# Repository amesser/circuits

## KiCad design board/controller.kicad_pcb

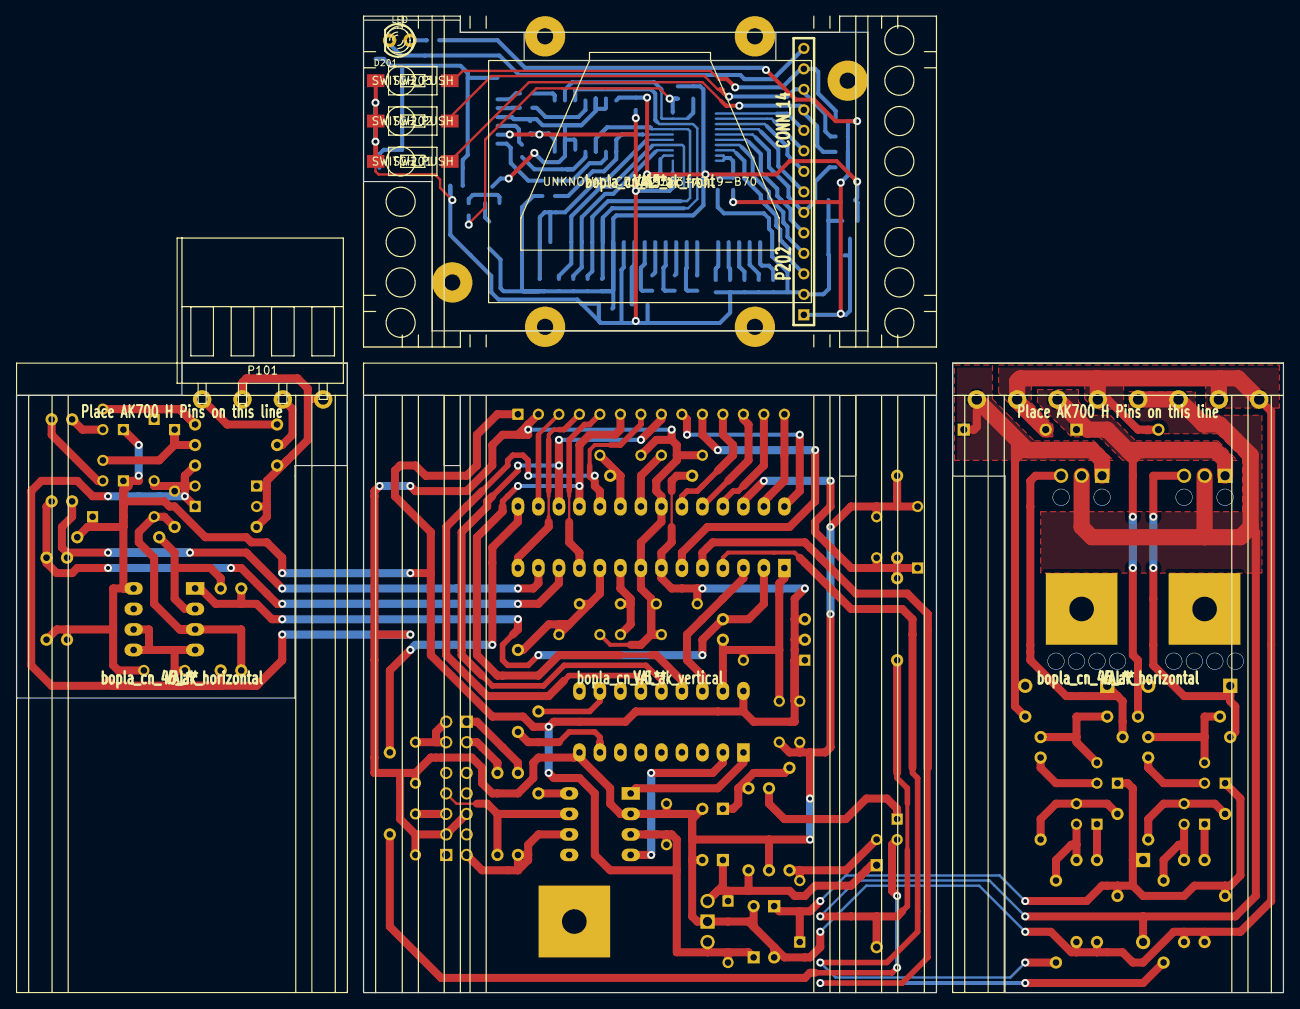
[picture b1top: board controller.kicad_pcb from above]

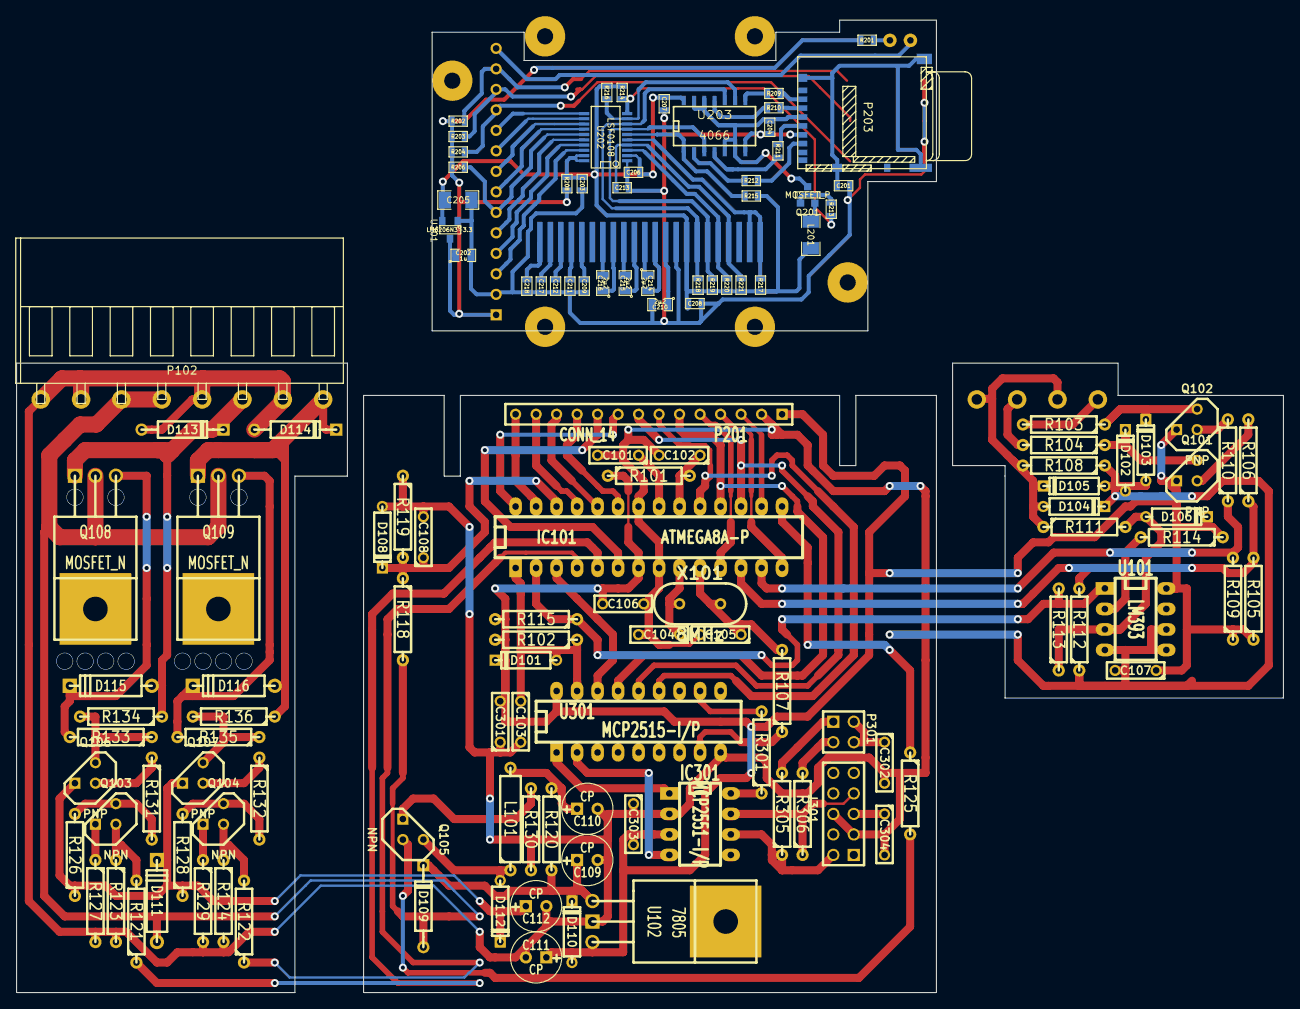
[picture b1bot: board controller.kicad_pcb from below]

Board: 2 copper layers, 157.0 x 120.5 mm, 142 parts (131 on the bottom side), 116 nets.

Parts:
C101, C102, C103, C106, C107, C108, C301, C302, C303, C304: 100n; C2
C104, C105: C; C2
C109, C110, C111, C112: CP; C1V7
C201, C203, C204, C206, C207, C208, C213: 100n; SM0603
C202: 1u; SM0805
C205: 10u; SM1206
C209, C211, C212, C217, C218: 1µ; SM0603
C210, C214, C215, C216: 2µ2; SM0805
D101, D104, D105, D106, D110, D112: DIODE; D3
D102, D103: ZENER; D3
D108: 4V7; D3
D109, D113, D114: DIODE; DO-41
D111, D115, D116: 12V; D4
D201: LED; LED-3MM
IC101: ATMEGA8A-P; DIP-28__300_ELL
IC301: MCP2551-I/P; DIP-8__300_ELL
J301: DB9; PIN_ARRAY_5x2
L101: 2.2mH; R5
L201: 47u; SM1206
LCD201: UNKNOWN_LCD_C39363-A319-B70; unkown_lcd_c39363-a319-b70
P101: CONN_4; bopla_ak700_4h
P102: CONN_8; bopla_ak700_8h
P201, P202: CONN_14; SIL-14
P203: MICROSD; hirose_dm3at
P301: CONN_2X2; PIN_ARRAY_2X2
Q101, Q102, Q106, Q107: PNP; TO92
Q103, Q104, Q105: NPN; TO92
Q108, Q109: MOSFET_N; TO220GDS
Q201: MOSFET_P; SOT23GDS
R101, R103, R104, R108, R120: 10; R4
R102, R105, R106, R109, R110, R111, R119, R125, R131, R132, R134, R136: 10k; R4
R107, R112, R114: R; R4
R113: 1M; R4
R115, R121, R122, R123, R124, R126, R127, R128, R129: 4k7; R4
R118: 33k; R4
R130: 470; R4
R133, R135, R301: 1k; R4
R201: 1k; SM0603
R202, R203, R204, R206, R213, R214, R215, R216, R217, R218, R219, R220, R221: 10k; SM0603
R208: 200k; SM0603
R209, R210, R211, R212: 10; SM0603
R305, R306: 60; R4
SW201, SW202, SW203: SWITCH_PUSH; te_fsmsm
U101: LM393; DIP-8__300_ELL
U102: 7805; LM78XX
U201: LM6206N3-3.3; SOT23
U202: LSF0108; SSOP20
U203: 4066; SO14N
U301: MCP2515-I/P; DIP-18__300_ELL
X101: 8MHz; HC-49V
bopla_cn_45_ak_front: VAL**; bopla_cn_45_ak_front_modified
bopla_cn_45_ak_horizontal, bopla_cn_45_ak_horizontal#2: VAL**; bopla_cn_45_ak_horizontal
bopla_cn_45_ak_vertical: VAL**; bopla_cn_45_ak_vertical

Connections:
+5V: C106.2, C107.1, C111.1, C301.2, C303.2, D101.2, D106.2, D110.1, IC101.7, IC301.3, P201.1, Q101.1, Q102.1, R101.1, R102.2, R105.1, R109.1, R114.1, R115.2, U101.8, U102.VO, U301.18
/CLKboost: IC101.15, R125.1
/Can Interface/CS: IC101.3, U301.16
/Can Interface/OSC1/CLK: R107.1, U301.8
/Can Interface/RESET: C103.1, D101.1, IC101.1, R102.1, U301.17
/Can Interface/SCK: IC101.19, P201.7, U301.13
/Can Interface/SI: IC101.17, P201.8, U301.14
/Can Interface/SO: IC101.18, P201.6, U301.15
/Display/A0_LCD: IC101.16, P201.3
/Display/CS_LCD: IC101.11, P201.5
/Display/CS_SD: IC101.28, P201.9
/Display/LED: IC101.27, P201.14
/Display/PWRE_SD: IC101.6, P201.10
/Display/RESET_LCD: IC101.14, P201.4
/Display/SW1: IC101.23, P201.11
/Display/SW2: IC101.24, P201.12
/Display/SW3: IC101.25, P201.13
/ESens_a: IC101.12, R105.2, R106.1
/ESens_b: IC101.13, R109.2, R110.1
/Echa: IC101.5, R121.1
/Echb: IC101.4, R122.1
/MVpwr: C108.1, D108.2, IC101.26, R118.1, R119.2
/RXD: IC101.2, R113.2, R115.1, U101.1
/Vboost: C112.1, D111.2, D112.2, Q106.1, Q107.1, R126.1, R128.1
/Vcha: D113.2, D115.1, P102.6, Q108.S, R134.1
/Vchb: D114.2, D116.1, P102.8, Q109.S, R136.1
/Vpwr: D109.1, D111.1, P102.3, P102.4, Q108.D, Q109.D, R118.2
/Vref: C101.1, IC101.21
GND: C101.2, C102.2, C103.2, C104.2, C105.2, C106.1, C107.2, C108.2, C109.2, C110.2, C111.2, C112.2, C201.2, C202.2, C203.2, C204.2, C205.2, C206.2, C207.2, C208.2, C209.2, C210.2, C211.2, C212.2, C213.2, C217.2, C218.2, C301.1, C302.2, C303.1, C304.2, D102.1, D103.1, D104.2, D105.1, D108.1, D113.1, D114.1, IC101.8, IC101.22, IC301.2, J301.3, J301.6, LCD201.9, P102.1, P102.2, P102.5, P102.7, P201.2, P202.2, P203.6, R108.1, R112.1, R119.1, R123.2, R124.2, R127.2, R129.2, R130.2, SW201.1, SW202.1, SW203.1, U101.4, U101.5, U101.6, U102.GND, U201.1, U202.1, U203.7, U301.9
unnamed: Q106.2, R131.1
unnamed: Q103.3, R126.2, R131.2
unnamed: Q103.1, R127.1
unnamed: Q103.2, R121.2, R123.1
unnamed: D116.2, Q109.G, R135.2
unnamed: Q105.2, R125.2
unnamed: Q105.1, R130.1
unnamed: C110.1, L101.2, R120.1
unnamed: D112.1, L101.1, Q105.3
unnamed: Q107.2, R132.1
unnamed: Q107.3, R135.1, R136.2
unnamed: Q104.3, R128.2, R132.2
unnamed: Q104.1, R129.1
unnamed: Q104.2, R122.2, R124.1
unnamed: P101.3, R104.2
unnamed: D102.2, Q101.3, R104.1
unnamed: D103.2, Q102.3, R103.1
unnamed: P101.1, R103.2
unnamed: Q101.2, R106.2
unnamed: D106.1, R111.2, R113.1, U101.3
unnamed: Q102.2, R110.2
unnamed: C105.1, IC101.10, R107.2, X101.2
unnamed: D115.2, Q108.G, R133.2
unnamed: Q106.3, R133.1, R134.2
unnamed: C102.1, IC101.20, R101.2
unnamed: C104.1, IC101.9, X101.1
unnamed: C109.1, D109.2, D110.2, R120.2, U102.VI
unnamed: R112.2, R114.2, U101.2
unnamed: D104.1, D105.2, P101.2, P101.4, R108.2, R111.1
unnamed: P301.1, R305.2
unnamed: IC301.8, R301.1
unnamed: R301.2, U301.11
unnamed: C304.1, J301.5
unnamed: P301.3, R306.2
unnamed: IC301.4, U301.2
unnamed: IC301.1, U301.1
unnamed: C302.1, P301.2, P301.4
unnamed: IC301.7, J301.7, R306.1
unnamed: IC301.6, J301.2, R305.1
unnamed: R209.1, U203.8
unnamed: P202.12, R203.1, SW202.2
unnamed: P202.13, R202.1, SW203.2
unnamed: C201.1, P203.S
unnamed: D201.2, P202.14
unnamed: LCD201.6, R219.2, U202.7, U203.3
unnamed: LCD201.7, R218.2, U202.8, U203.10
unnamed: R215.2, U202.6, U203.1
unnamed: R216.2, U202.9, U203.9
unnamed: C213.1, LCD201.4, R221.2, U202.4
unnamed: LCD201.5, R220.2, U202.3
unnamed: C205.1, C206.1, C207.1, C208.1, L201.1, LCD201.8, R214.1, R215.1, R216.1, R217.1, R218.1, R219.1, R220.1, R221.1, U201.2, U202.2, U203.14
unnamed: C215.1, LCD201.13
unnamed: C218.1, LCD201.22
unnamed: C214.1, LCD201.12
unnamed: C217.1, LCD201.21
unnamed: C214.2, LCD201.11
unnamed: C212.1, LCD201.20
unnamed: C215.2, LCD201.14
unnamed: LCD201.1, LCD201.2, R217.2, U202.5
unnamed: C216.1, LCD201.15
unnamed: C216.2, LCD201.16
unnamed: C209.1, LCD201.18
unnamed: C211.1, LCD201.19
unnamed: C203.1, R208.2, U202.19, U202.20
unnamed: P203.7, R212.2
unnamed: R212.1, U203.2
unnamed: P203.5, R211.2
unnamed: R211.1, U203.4
unnamed: P203.3, R210.2
unnamed: R210.1, U203.11
unnamed: P203.2, R209.2
unnamed: Q201.G, R213.2
unnamed: L201.2, Q201.S
unnamed: C210.1, LCD201.10
unnamed: D201.1, R201.1
unnamed: P202.3, U202.18
unnamed: P202.4, U202.17
unnamed: P202.5, U202.16
unnamed: R213.1, R214.2, U202.10
unnamed: P202.11, R204.1, SW201.2
unnamed: P202.10, U202.11
unnamed: P202.9, U202.12
unnamed: P202.8, U202.13
unnamed: P202.7, U202.14
unnamed: P202.6, R206.1, U202.15
unnamed: C202.1, P202.1, R201.2, R202.2, R203.2, R204.2, R206.2, R208.1, U201.3
unnamed: C204.1, P203.4, Q201.D, U203.5, U203.6, U203.12, U203.13

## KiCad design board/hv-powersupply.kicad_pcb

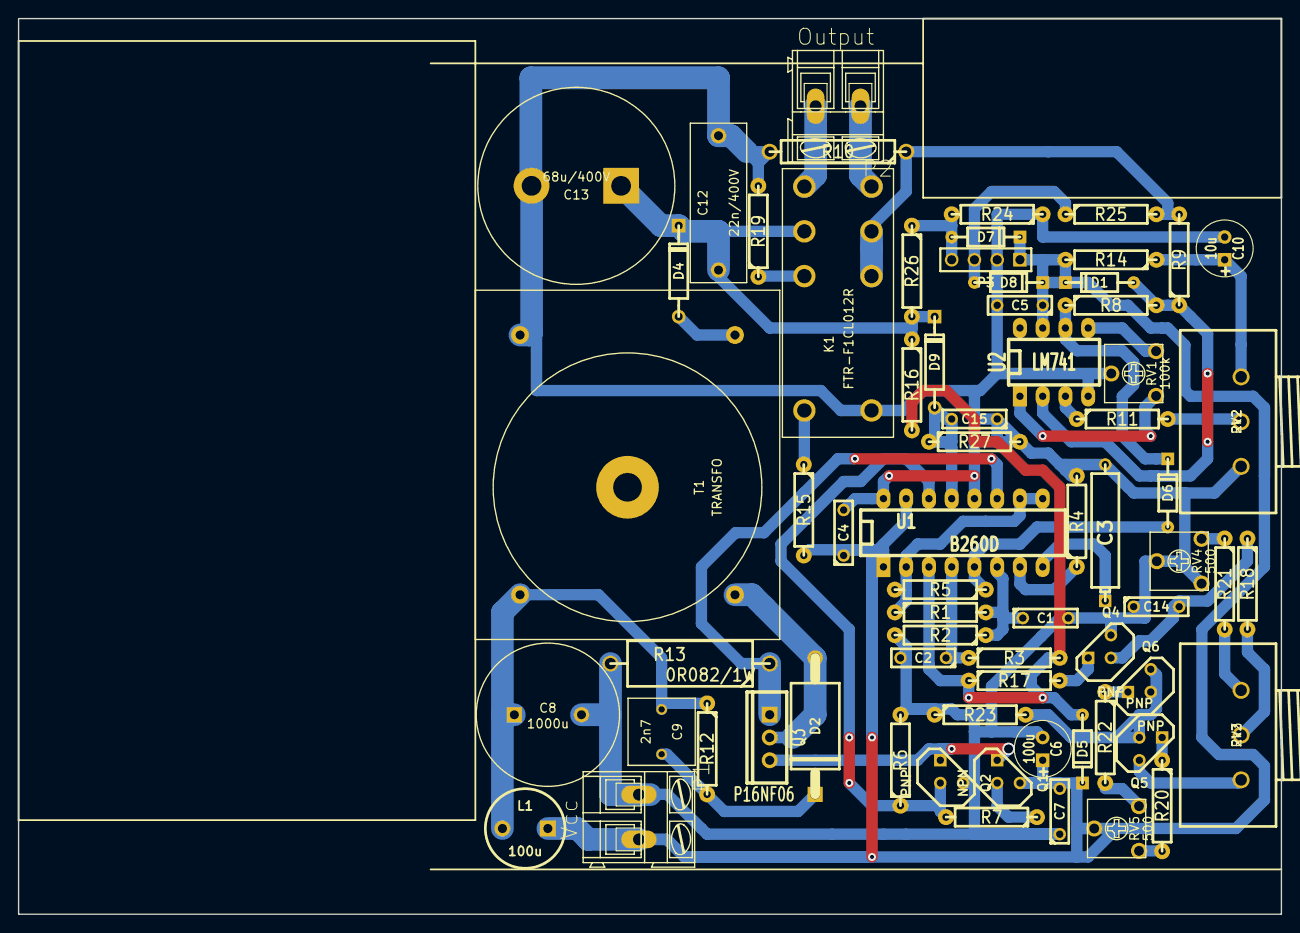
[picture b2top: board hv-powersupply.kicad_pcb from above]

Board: 2 copper layers, 141.0 x 100.0 mm, 68 parts (0 on the bottom side), 44 nets.

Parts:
C1, C4, C5, C7, C14, C15: 100n; C2
C2: 22n; C2
C3: 3n3; CP6
C6: 100u; C1V7
C8: 1000u; cp_radial_rm75_160
C9: 2n7; mkp_1837_75
C10: 10u; C1V7
C12: 22n/400V; mkp_1844_178x63
C13: 68u/400V; cp_snapin_rm10_220
D1, D5, D6, D7, D8: DIODE; DO-35
D2: BY296; DO-201
D4: BYT 11-1000; DO-41
D9: 250V/0.5W; DO-41
K1: FTR-F1CL012R; relay-2dt-rm
L1: 100u; C2V8
P1: Vcc; AK300-2
P2: Output; AK300-2
P3: CONN_4; PIN_ARRAY_4x1
Q1: NPN; TO92
Q2, Q4, Q5, Q6: PNP; TO92
Q3: P16NF06; TO220GDS_VERT
R1, R20, R22, R23: 6k8; R4-LARGE_PADS
R2: 10k; R4-LARGE_PADS
R3, R8, R26: 220k; R4-LARGE_PADS
R4: 17k8; R4-LARGE_PADS
R5: 22k; R4-LARGE_PADS
R6, R7, R9, R11, R17, R18, R24, R25: 2k2; R4-LARGE_PADS
R10: 10; R6
R12: 470; R4-LARGE_PADS
R13: 0R082/1W; R7
R14: 15k; R4-LARGE_PADS
R15: 100; R4-LARGE_PADS
R16: 220k/0.5W; R4-LARGE_PADS
R19: 1k; R4-LARGE_PADS
R21, R27: 510; R4-LARGE_PADS
RV1: 100k; pot_acp_ca6_v5
RV2, RV3: 2k2; pot_omeg_pc20bu
RV4, RV5: 500; pot_acp_ca6_v5
T1: TRANSFO; transformer-ddr-smps
U1: B260D; DIP-16__300_ELL
U2: LM741; DIP-8__300_ELL

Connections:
+15V: C4.1, C5.1, C6.1, C7.2, D1.2, D5.2, D7.2, D8.2, L1.1, P1.2, P3.1, Q1.3, R14.2, R15.2, RV5.2, U1.1, U1.15, U2.7
/VOUT+: C12.1, C13.1, D4.2, D9.2, K1.11, R16.1, R26.2
/VOUT-: K1.21, K1.22, R9.2, R10.1, R25.2
GND: C1.2, C2.2, C3.2, C4.2, C5.2, C6.2, C7.1, C8.2, C10.2, C12.2, C13.2, C14.1, C15.1, K1.A2, P1.1, P3.2, Q2.3, Q4.3, R2.2, R4.2, R6.2, R10.2, R13.2, R19.2, R23.1, R24.1, R27.2, RV1.2, RV2.3, RV4.1, RV4.2, T1.2, U1.12, U1.16, U2.4
unnamed: C2.1, R3.1, U1.4
unnamed: Q3.S, R13.1, U1.11
unnamed: Q5.3, RV3.3
unnamed: C1.1, R1.2, R2.1, U1.6
unnamed: R21.2, RV3.1
unnamed: D6.1, R5.1, U1.5
unnamed: R1.1, R5.2, U1.2, U1.9, U1.10
unnamed: C9.2, D2.2, R12.2
unnamed: Q1.1, Q2.1, Q3.G
unnamed: D2.1, Q3.D, T1.3
unnamed: R4.1, U1.7
unnamed: C3.1, U1.8
unnamed: C15.2, D9.1, R27.1, U1.13
unnamed: Q1.2, R7.1
unnamed: Q4.1, R17.2
unnamed: D5.1, R3.2, R16.2, R17.1, U1.3
unnamed: D4.1, T1.1
unnamed: C8.1, C9.1, L1.2, R12.1, T1.4
unnamed: D7.1, P3.4, R24.2, R26.1
unnamed: D8.1, P3.3, R25.1
unnamed: K1.A1, R15.1
unnamed: D6.2, R8.1, U2.6
unnamed: K1.14, P2.2
unnamed: K1.24, P2.1
unnamed: K1.12, R19.1
unnamed: Q2.2, R6.1, R7.2, U1.14
unnamed: RV1.1, U2.1
unnamed: RV1.3, U2.5
unnamed: D1.1, R8.2, R9.1, U2.2
unnamed: C10.1, R14.1, RV2.1
unnamed: R11.1, U2.3
unnamed: Q5.1, R20.1
unnamed: R20.2, RV5.1
unnamed: R22.2, RV5.3
unnamed: Q5.2, Q6.2, Q6.3, R23.2
unnamed: Q6.1, R22.1
unnamed: R21.1, RV4.3
unnamed: R18.2, RV3.2
unnamed: C14.2, Q4.2, R18.1
unnamed: R11.2, RV2.2

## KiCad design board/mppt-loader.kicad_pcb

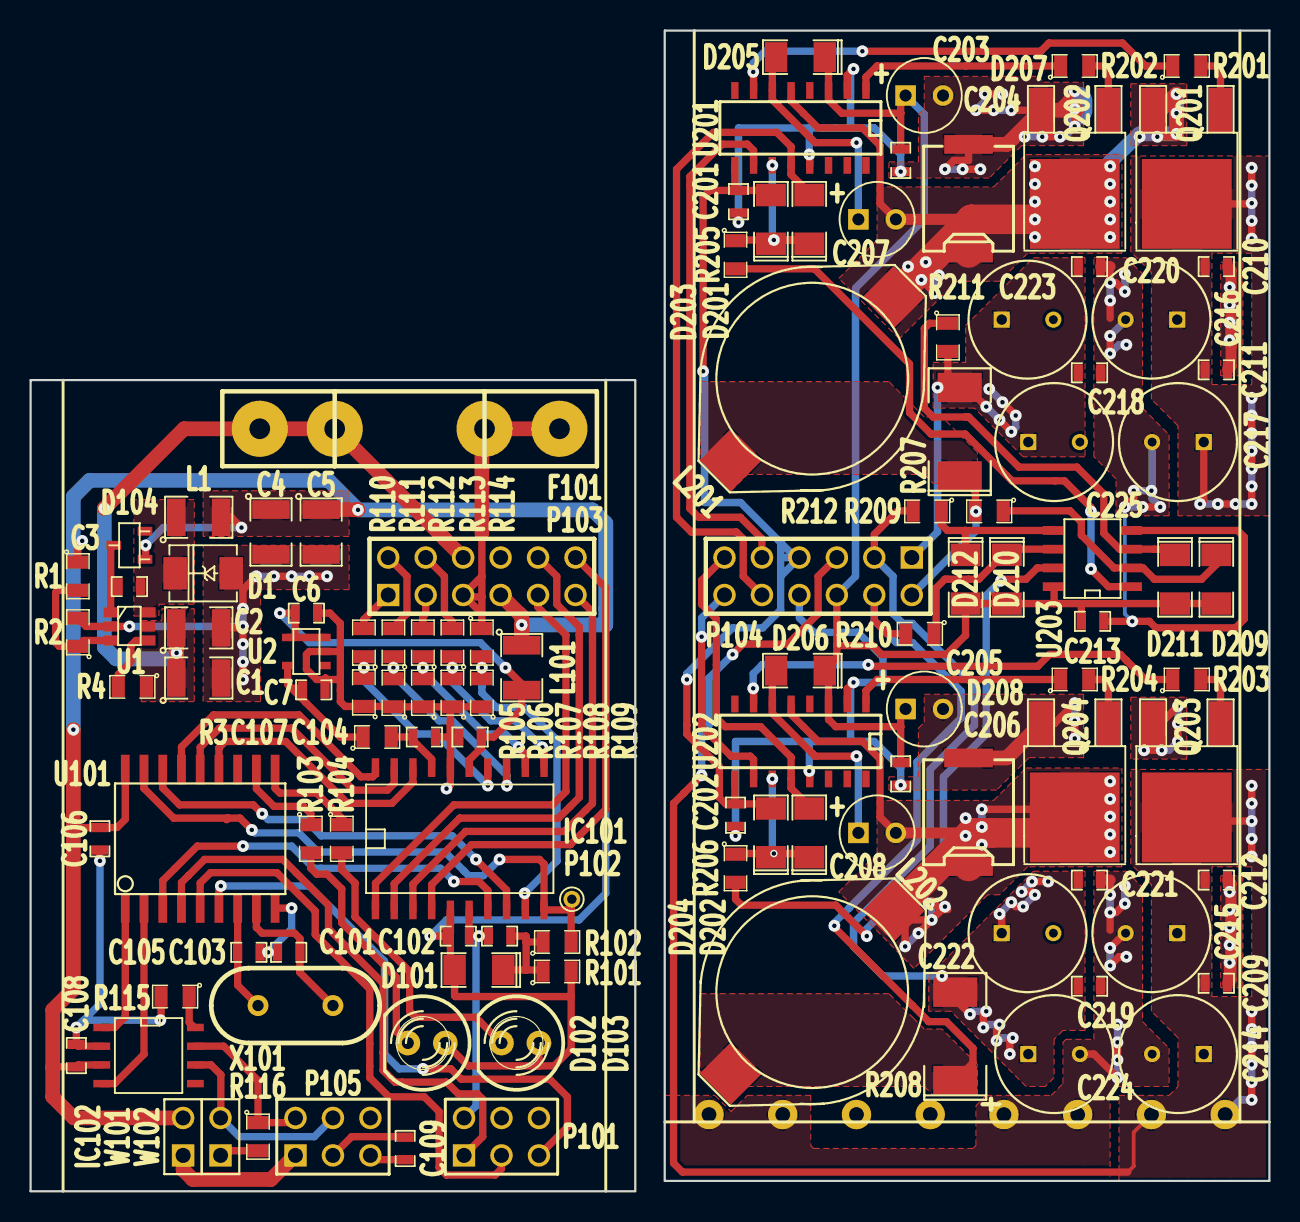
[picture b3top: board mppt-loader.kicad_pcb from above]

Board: 2 copper layers, 84.0 x 78.7 mm, 116 parts (1 on the bottom side), 79 nets.

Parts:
C1, C2, C4, C5: 10u; SM1210
C3, C6, C101, C102, C104, C106, C107, C108, C109, C201, C202, C204, C206, C209, C210, C211, C212, C213, C218, C219, C220, C221: 100n; SM0603_Capa
C7: 22n; SM0603_Capa
C103, C105: 22p; SM0603_Capa
C203, C205, C207, C208: 10u; C1V5
C214, C215, C216, C217, C222, C223, C224, C225: 100u; cp_radial_rm35_80
D1: DIODESCH; DO-214AC(SMA)
D101, D201, D202, D203, D204, D205, D206, D209, D210, D211, D212: DIODE; SM1206POL
D102, D103: LED; LED-5MM
D104: 1N4148; sot23
D207, D208: DIODESCH; SMD403
F101: FUSE; FUSE5-20
IC101: ATTINY461A-S; SO20L
IC102: MCP2551-I/SN; SO8N
L1, L101: 22u; SM1210
L201, L202: 22u; fastron_pisr
P101: CONN_3X2; pin_array_3x2
P102: TST; PINTST
P103, P104: CONN_12; pin_array_6x2
P105: CONN_5; pin_array_3x2
P106: CONN_8; bopla_ak700_8h
Q201, Q202, Q203, Q204: IRLU024N; DPAKGDS
R1: 52k3; SM0805
R2, R102, R110, R111, R112, R113, R114, R209, R210, R211, R212: 10k; SM0805
R3: 100; SM0805
R4: 1M; SM0805
R101, R116: 120; SM0805
R103, R104, R105, R106, R107, R108, R109, R115, R205, R206: 1k; SM0805
R201, R202, R203, R204: 10; SM0805
R207, R208: 0R1; SM2512
U1: MCP16301; SOT23_6
U2: LM4132-2.5; SOT23-5
U101: MCP2515; SOIC18W
U201, U202: IR2110; SO16E
U203: LM393; SO8E
W101, W102: TEST; PIN_ARRAY_2X1
X101: 8MHz; HC-49V

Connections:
+5V: C4.1, C5.1, C101.1, C106.2, C108.2, D101.2, D102.1, D103.1, D104.1, IC101.5, IC102.3, L1.2, L101.1, P103.7, R1.1, R101.2, U101.18, W101.2
/AVCC: C6.1, C104.1, IC101.15, L101.2, U2.3, U2.4
/CAN_CS: IC101.8, U101.16
/CAN_SCK: IC101.18, U101.13
/CAN_SI: IC101.19, U101.14
/CAN_SO: IC101.20, U101.15
/CLK: IC101.7, U101.3
/Powerstage/GND_LOGIC: C201.1, C202.1, C203.2, C204.2, C205.2, C206.2, C209.2, C210.2, C211.2, C212.2, C213.1, C214.2, C215.2, C216.2, C217.2, C218.2, C219.2, C220.2, C221.2, C222.2, C223.2, C224.2, C225.2, D207.1, D208.1, P104.8, P106.1, P106.2, P106.5, P106.6, Q202.S, Q204.S, U201.2, U201.13, U202.2, U202.13, U203.4
/Powerstage/HIGHSIDEA: P104.9, U201.10
/Powerstage/HIGHSIDEB: P104.12, U202.10
/Powerstage/LOWSIDEA: D201.2, P104.10, U201.12
/Powerstage/LOWSIDEB: D202.2, P104.11, U202.12
/Powerstage/SENSEA_I: L201.2, P104.2, R207.1, R209.2
/Powerstage/SENSEA_VOUT: C218.1, C219.1, C220.1, C221.1, C222.1, C223.1, C224.1, C225.1, P104.1, P104.3, P106.3, P106.4, R207.2, R208.2, R211.2, R212.2
/Powerstage/SENSEB_I: L202.2, P104.4, R208.1, R210.2
/Powerstage/VDD_LOGIC: C201.2, C202.2, D203.2, D204.2, P104.7, U201.9, U202.9
/Powerstage/VDD_PWR: C203.1, C204.1, C205.1, C206.1, C213.2, D205.1, D206.1, D209.2, D210.2, D211.2, D212.2, P104.6, U201.3, U202.3, U203.8
/Powerstage/VINA: C209.1, C210.1, C211.1, C212.1, C214.1, C215.1, C216.1, C217.1, P104.5, P106.7, P106.8, Q201.D, Q203.D
/Powerstage/VSA: C207.2, D207.2, L201.1, Q201.S, Q202.D, U201.5
/Powerstage/VSB: C208.2, D208.2, L202.1, Q203.S, Q204.D, U202.5
/RESET: IC101.10, P102.1, R102.2, U101.17
/VBAT: F101.1, P103.5, R114.1
/VDDPWR: C1.1, C2.1, F101.2, P103.6, R4.1, U1.5
/VREF: C107.1, IC101.17, R3.2
DGND: C1.2, C2.2, C4.2, C5.2, C6.2, C7.2, C101.2, C102.2, C103.2, C104.2, C105.2, C106.1, C107.2, C108.1, C109.1, D1.1, IC101.6, IC101.16, IC102.2, P101.2, P101.4, P101.6, P103.8, P105.5, R2.2, R105.1, R106.1, R107.1, R108.1, R109.1, R115.2, U1.2, U2.2, U101.9
unnamed: IC101.2, P103.10
unnamed: IC101.4, P103.12
unnamed: IC101.3, P103.11
unnamed: IC101.1, P103.9
unnamed: IC101.9, R109.2, R114.2
unnamed: C105.1, U101.7, X101.2
unnamed: P103.4, R113.2
unnamed: P103.3, R112.2
unnamed: P103.2, R111.2
unnamed: IC101.13, R106.2, R111.1
unnamed: IC101.12, R107.2, R112.1
unnamed: IC101.11, R108.2, R113.1
unnamed: P105.1, W101.1
unnamed: C7.1, R3.1, U2.5
unnamed: R1.2, R2.1, U1.3
unnamed: R4.2, U1.4
unnamed: C3.1, D104.2, U1.1
unnamed: C3.2, D1.2, L1.1, U1.6
unnamed: C109.2, P105.3
unnamed: IC102.7, P105.2, R116.1
unnamed: R116.2, W102.1
unnamed: IC102.6, P105.4, W102.2
unnamed: IC102.8, R115.1
unnamed: IC102.1, U101.1
unnamed: IC102.4, U101.2
unnamed: C102.1, D101.1, R101.1, R102.1
unnamed: C103.1, U101.8, X101.1
unnamed: P103.1, R110.2
unnamed: IC101.14, R105.2, R110.1
unnamed: R103.1, U101.11
unnamed: P101.1, U101.4
unnamed: P101.3, U101.5
unnamed: P101.5, U101.6
unnamed: D102.2, R103.2
unnamed: R104.1, U101.10
unnamed: D103.2, R104.2
unnamed: D211.1, R211.1, U203.3
unnamed: D209.1, R209.1, U203.2
unnamed: R205.2, U203.1
unnamed: D202.1, D204.1, R206.1, U202.11
unnamed: R206.2, U203.7
unnamed: D212.1, R212.1, U203.5
unnamed: D210.1, R210.1, U203.6
unnamed: R204.1, U202.1
unnamed: C208.1, D206.2, U202.6
unnamed: R203.1, U202.7
unnamed: Q203.G, R203.2
unnamed: Q204.G, R204.2
unnamed: Q202.G, R202.2
unnamed: Q201.G, R201.2
unnamed: D201.1, D203.1, R205.1, U201.11
unnamed: R202.1, U201.1
unnamed: C207.1, D205.2, U201.6
unnamed: R201.1, U201.7

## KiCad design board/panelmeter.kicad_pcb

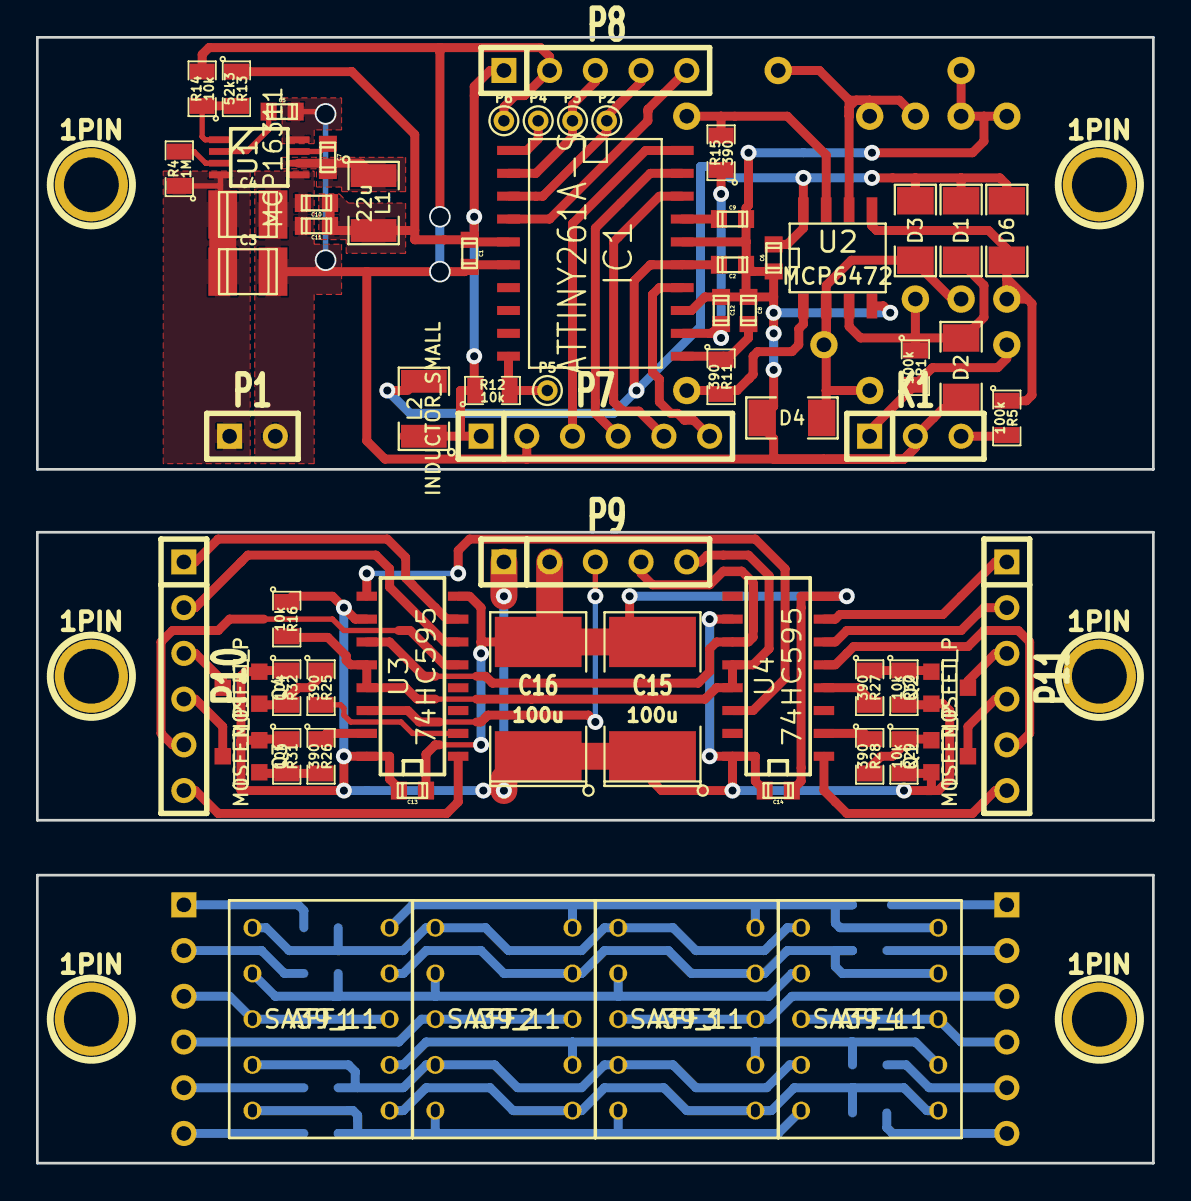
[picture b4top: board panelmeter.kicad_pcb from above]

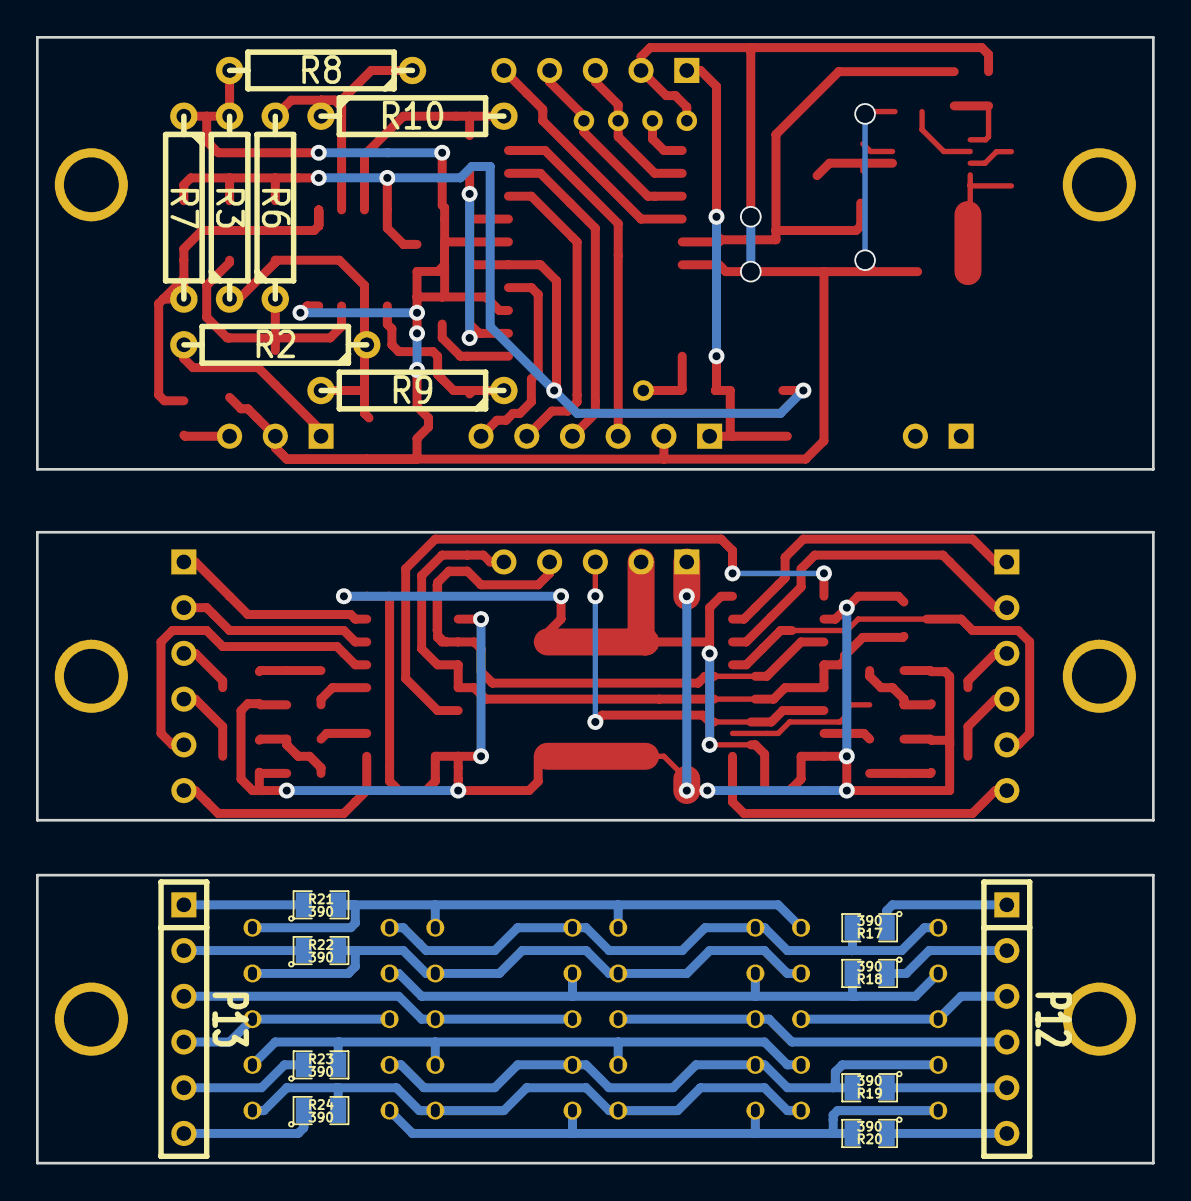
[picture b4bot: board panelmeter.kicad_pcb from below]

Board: 2 copper layers, 62.0 x 62.5 mm, 88 parts (17 on the bottom side), 74 nets.

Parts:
1PIN, 1PIN#2, 1PIN#3, 1PIN#4, 1PIN#5, 1PIN#6: P***; 1pin
AFF1, AFF2, AFF3, AFF4: SA39_11; KINGBRIGHT_SA39_11
C1, C2, C6, C7, C9, C13, C14: 100n; c_0603
C3, C4: 10u; c_1210
C5: 1u; c_0603
C8, C12: 1n; c_0603
C10, C11: 10u/6.3V; c_0603
C15, C16: 100u; SM2112L
D1, D2, D3, D4, D6: DIODE; SM1206
IC1: ATTINY261A-S; SO20L
K1: CONN_3; SIL-3
L1: 22u; SM1210
L2: INDUCTOR_SMALL; SM1210
P1: CONN_2; SIL-2
P2, P3, P4, P5, P6: TST; PINTST
P7, P10, P11, P12, P13: CONN_6; SIL-6
P8, P9: CONN_5; SIL-5
Q1, Q2, Q3, Q4: MOSFET_P; SOT23GDS
R1, R5: 100k; SM0805
R2, R3, R8, R9: 100k; R4
R4: 1M; SM0805
R6, R7, R10: 0; R4
R11, R15, R17, R18, R19, R20, R21, R22, R23, R24, R25, R26, R27, R28: 390; SM0805
R12, R14, R16, R29, R30, R31, R32: 10k; SM0805
R13: 52k3; SM0805
U1: MCP16311; MSOP_8
U2: MCP6472; SO8E
U3, U4: 74HC595; SO16E

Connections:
+5V: C1.2, C10.2, C11.2, IC1.5, L1.2, L2.1, P7.1, P8.1, R12.1, R13.1
+5VA: C2.1, C6.1, D1.2, D3.2, D6.2, IC1.15, L2.2, U2.8
/ADC0: C12.1, IC1.12, R15.1
/ADC1: C8.1, IC1.11, R11.1
/DIG_1: R25.2, U3.2
/DIG_2: R26.1, U3.15
/DIG_3: R27.2, U4.4
/DIG_4: R28.1, U4.2
/SEG_A: P11.1, U4.7
/SEG_B: P11.2, U4.6
/SEG_C: P11.5, U4.5
/SEG_D: P10.6, U3.1
/SEG_DP: P11.6, U4.1
/SEG_E: P10.5, U3.5
/SEG_F: P10.2, U3.6
/SEG_G: P10.1, U3.7
GND: C1.1, C2.2, C3.1, C4.1, C5.1, C6.2, C8.2, C9.1, C10.1, C11.1, C12.2, C13.2, C14.2, C15.2, C16.2, D2.1, D4.1, IC1.6, IC1.13, IC1.16, K1.2, P1.2, P6.1, P7.2, P8.2, P9.2, R3.2, R7.1, R8.2, R14.2, U1.5, U1.8, U2.4, U3.8, U4.8
unnamed: P10.3, Q4.D
unnamed: Q2.G, R27.1, R30.1
unnamed: Q1.G, R28.2, R29.1
unnamed: AFF3.3, AFF3.8, P13.3
unnamed: IC1.10, P5.1, R12.2
unnamed: IC1.1, P4.1
unnamed: P9.5, R16.2, U3.12, U3.13, U4.12, U4.13
unnamed: P9.3, U3.14
unnamed: P9.4, U3.11, U4.11
unnamed: Q3.G, R26.2, R31.2
unnamed: IC1.4, P8.5
unnamed: IC1.3, P2.1, P8.4
unnamed: IC1.2, P3.1, P8.3
unnamed: C7.2, U1.7
unnamed: C7.1, L1.1, U1.6
unnamed: R4.2, U1.3
unnamed: C3.2, C4.2, P1.1, R4.1, U1.4
unnamed: C5.2, U1.2
unnamed: R13.2, R14.1, U1.1
unnamed: K1.3, R5.2
unnamed: U3.9, U4.14
unnamed: Q4.G, R25.1, R32.2
unnamed: R9.1, R11.2, U2.1
unnamed: K1.1, R1.2, R2.2
unnamed: AFF2.3, AFF2.8, P12.4
unnamed: AFF4.3, AFF4.8, P13.4
unnamed: P12.2, R18.1
unnamed: P12.5, R19.1
unnamed: P12.6, R20.1
unnamed: P13.1, R21.1
unnamed: P13.2, R22.1
unnamed: P13.5, R23.1
unnamed: P13.6, R24.1
unnamed: P10.4, Q3.D
unnamed: P12.1, R17.1
unnamed: R10.2, R15.2, U2.7
unnamed: D3.1, D4.2, R2.1, R3.1, R9.2, U2.2
unnamed: R6.2, R8.1, R10.1, U2.6
unnamed: IC1.20, P7.3
unnamed: IC1.19, P7.4
unnamed: IC1.18, P7.5
unnamed: IC1.14, P7.6
unnamed: D1.1, D2.2, R1.1, R6.1, U2.3
unnamed: D6.1, R5.1, R7.2, U2.5
unnamed: C9.2, IC1.17
unnamed: AFF1.4, AFF2.4, AFF3.4, AFF4.4, R19.2
unnamed: AFF1.6, AFF2.6, AFF3.6, AFF4.6, R24.2
unnamed: AFF1.7, AFF2.7, AFF3.7, AFF4.7, R23.2
unnamed: AFF1.1, AFF2.1, AFF3.1, AFF4.1, R17.2
unnamed: AFF1.2, AFF2.2, AFF3.2, AFF4.2, R18.2
unnamed: AFF1.5, AFF2.5, AFF3.5, AFF4.5, R20.2
unnamed: AFF1.9, AFF2.9, AFF3.9, AFF4.9, R22.2
unnamed: AFF1.10, AFF2.10, AFF3.10, AFF4.10, R21.2
unnamed: AFF1.3, AFF1.8, P12.3
unnamed: P11.4, Q1.D
unnamed: P11.3, Q2.D
VCC: C13.1, C14.1, C15.1, C16.1, P9.1, Q1.S, Q2.S, Q3.S, Q4.S, R16.1, R29.2, R30.2, R31.1, R32.1, U3.10, U3.16, U4.10, U4.16

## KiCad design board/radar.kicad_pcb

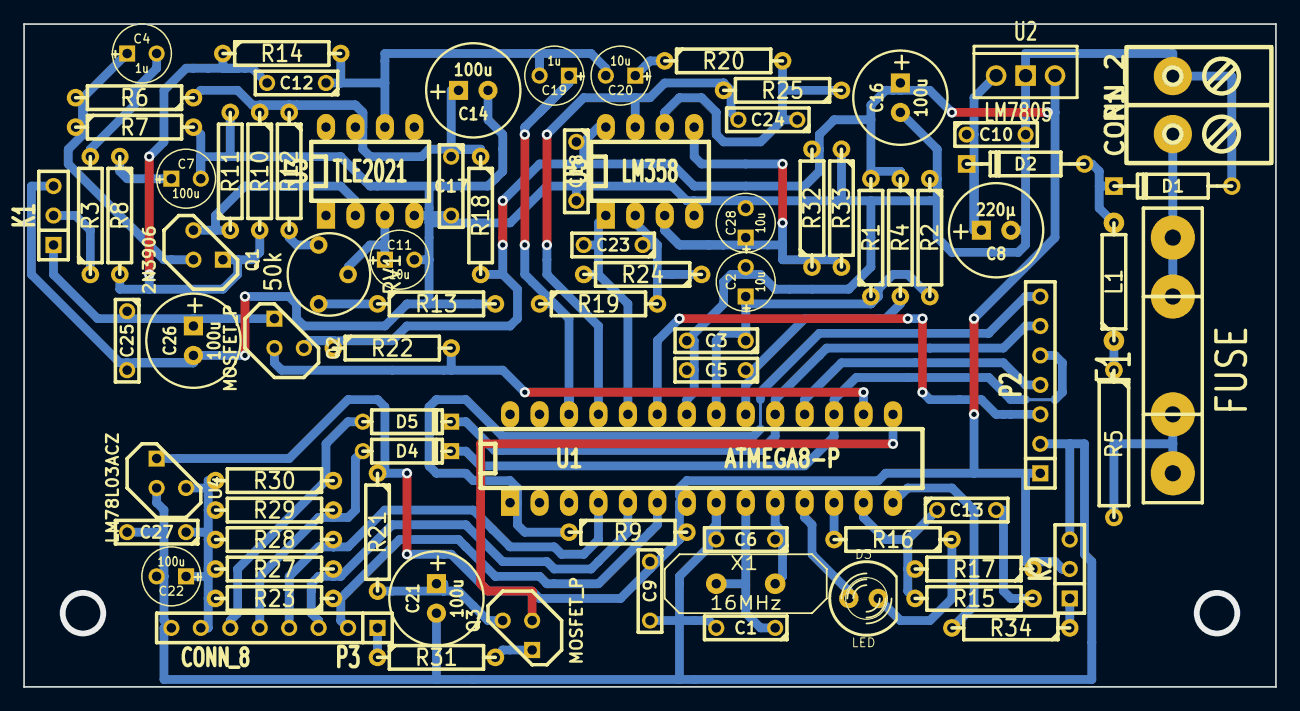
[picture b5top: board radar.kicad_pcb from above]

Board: 2 copper layers, 108.0 x 57.1 mm, 82 parts (0 on the bottom side), 52 nets.

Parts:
C1, C6: 10p; C2
C2, C11, C20, C28: 10u; C1V5
C3, C5, C9, C10, C13, C17, C18, C25, C27: 100n; C2
C4, C19: 1u; C1V5
C7, C22: 100u; C1V5
C8: 220µ; C1V8
C12, C23, C24: 1n; C2
C14, C16, C21, C26: 100u; C1V8
D1: ZENER; DO-41
D2: DIODE; DO-41
D3: LED; LED-5MM
D4, D5: DIODE; D3
F1: FUSE; FUSE5-20
K1, K2: CONN_3; SIL-3
L1: 47µ; R4-LARGE_PADS
P1: CONN_2; RIACON_007-2
P2: CONN_7; SIL-7
P3: CONN_8; SIL-8
Q1: 2N3906; TO92-INVERT
Q2, Q3: MOSFET_P; TO92DGS
R1, R10, R13, R33: 22k; R4
R2: 33k; R4
R3, R15, R20: 1k; R4
R4, R34: 100; R4
R5: 1; R5
R6, R9, R12, R14, R17, R22, R24, R32: 47k; R4
R7, R11, R25: 100k; R4
R8, R18: 47; R4
R16, R31: 150; R4
R19, R23, R27, R28, R29, R30: 4k7; R4
R21: 10; R4
RV1: 50k; RV2
U1: ATMEGA8-P; DIP-28__300_ELL
U2: LM7805; LM78XXV
U3: TLE2021; DIP-8__300_ELL
U4: LM78L03ACZ; TO92
U5: LM358; DIP-8__300_ELL
X1: 16MHz; HC-18UV

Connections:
+5V: C9.1, C16.1, C18.1, K2.2, P2.1, Q2.S, R1.2, R4.1, R9.2, R17.1, R18.2, R21.1, R22.1, R32.2, U1.7, U2.VO, U4.1, U5.8
/DISPLAY_CS: P3.3, R27.1, U1.5
/DISPLAY_DC: P3.4, R28.1, U1.4
/DISPLAY_LED: Q3.G, U1.15
/DISPLAY_RST: P3.2, R23.1, U1.6
/KEYBOARD: P2.3, U1.23
/MISO: P2.4, U1.18
/MOSI: D4.2, P2.5, U1.17
/OUTPUT: R34.2, U1.14
/RADAR_EN: Q2.G, R22.2, U1.16
/RESET: P2.7, R9.1, U1.1
/SCK: D5.2, P2.6, U1.19
/radar_60db: C19.1, R19.1, U1.26
/radar_80db: C23.2, R24.2, U1.24, U5.1
/radar_100db: C24.2, R25.2, U1.25, U5.7
/radar_out: K1.2, R3.1
GND: C1.2, C2.2, C3.2, C5.2, C6.2, C7.2, C8.2, C9.2, C10.2, C11.2, C13.2, C14.2, C16.2, C17.2, C18.2, C21.2, C22.2, C25.2, C26.2, C27.2, C28.2, D1.1, K1.3, K2.3, P1.2, P2.2, P3.8, R2.1, R7.2, R11.2, R13.2, R15.1, R33.1, U1.8, U1.22, U2.GND, U3.4, U4.2, U5.4
unnamed: C21.1, Q3.S, R21.2
unnamed: P3.1, R31.1
unnamed: D5.1, P3.6, R30.1
unnamed: C22.1, C27.1, P3.7, R23.2, R27.2, R28.2, R29.2, R30.2, U4.3
unnamed: D4.1, P3.5, R29.1
unnamed: C1.1, U1.9, X1.1
unnamed: C6.1, U1.10, X1.2
unnamed: C2.1, C3.1, R1.1, R2.2, U1.21
unnamed: D3.2, R16.1
unnamed: R16.2, U1.12
unnamed: Q3.D, R31.2
unnamed: C5.1, R4.2, U1.20
unnamed: D3.1, U1.11
unnamed: D1.2, D2.1, L1.2
unnamed: L1.1, R5.1
unnamed: F1.2, R5.2
unnamed: F1.1, P1.1
unnamed: K2.1, R34.1
unnamed: C13.1, R15.2, R17.2, U1.13
unnamed: C8.1, C10.1, D2.2, U2.VI
unnamed: C20.1, R20.1
unnamed: C24.1, R20.2, R25.1, U5.6
unnamed: C25.1, C26.1, K1.1, Q2.D
unnamed: C12.2, Q1.1, R8.2, R10.2, R14.1
unnamed: C4.2, R3.2
unnamed: R12.2, RV1.1
unnamed: R13.1, RV1.3
unnamed: C12.1, C19.2, C20.2, R14.2, U3.6
unnamed: C11.1, RV1.2, U3.3
unnamed: C14.1, C17.1, R6.1, R10.1, R12.1, R18.1, U3.7
unnamed: Q1.3, R11.1, U3.2
unnamed: C7.1, R8.1
unnamed: C28.1, R32.1, R33.2, U5.3, U5.5
unnamed: C4.1, Q1.2, R6.2, R7.1
unnamed: C23.1, R19.2, R24.1, U5.2

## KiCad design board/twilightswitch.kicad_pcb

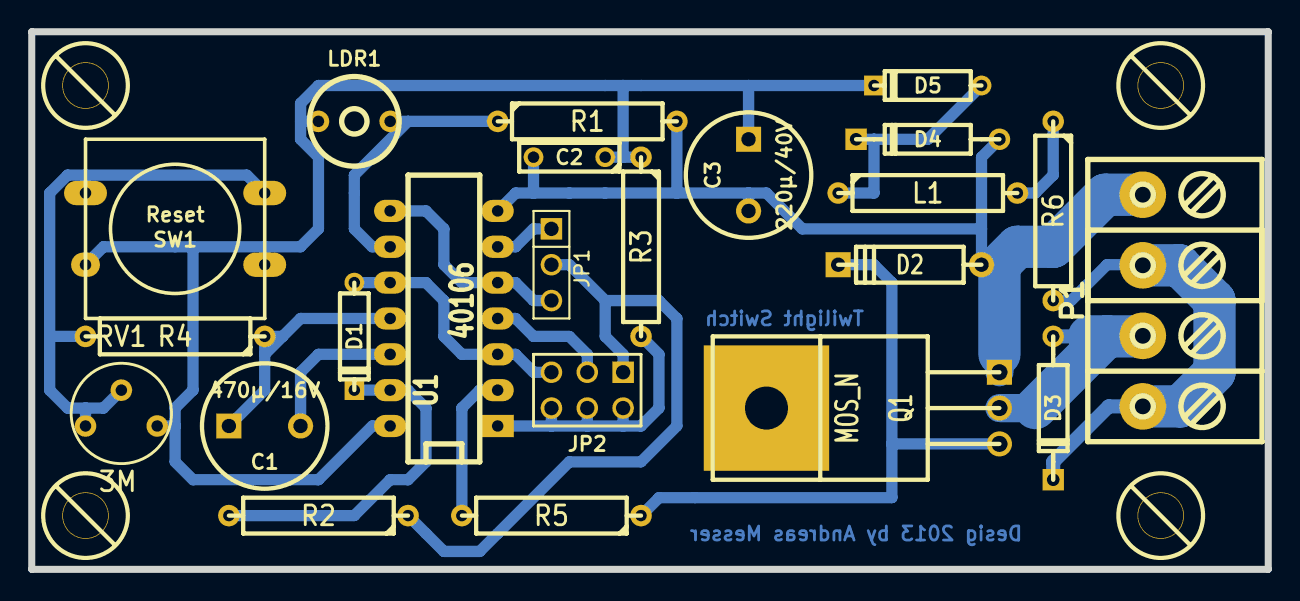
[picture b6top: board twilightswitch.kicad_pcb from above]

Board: 2 copper layers, 87.6 x 38.1 mm, 27 parts (0 on the bottom side), 19 nets.

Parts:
C1: 470µ/16V; C2V8
C2: 100n; C2
C3: 220µ/40V; C2V8
D1, D5: DIODE; D3
D2: 12V; D4
D3: DIODE; DO-41
D4: LPD; DO-41
HOLE_M3, HOLE_M3#2, HOLE_M3#3, HOLE_M3#4: VAL**; HOLE_M3
JP1: JUMPER3; PIN_ARRAY_3X1
JP2: CONN_3X2; pin_array_3x2
L1: 47µ; R5
LDR1: R; CV3-30PF
P1: CONN_4; RIACON_007-4
Q1: MOS_N; TO220GDS
R1, R2, R3: 57k; R5
R4: 1k; R5
R5, R6: 100; R5
RV1: 3M; RV2
SW1: Reset; SW_PUSH-12mm
U1: 40106; DIP-14__300_ELL

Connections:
unnamed: D3.1, P1.2, Q1.D
unnamed: L1.2, R6.1
unnamed: R5.2, U1.2
unnamed: LDR1.2, R1.1, U1.9
unnamed: C1.2, U1.12
unnamed: D1.2, R2.2, U1.13
unnamed: JP1.1, U1.6
unnamed: D2.2, Q1.G, R5.1
unnamed: D3.2, P1.1, P1.3, R6.2
unnamed: D4.2, D5.1, L1.1
unnamed: C1.1, R4.1, U1.11
unnamed: R4.2, RV1.1, RV1.2, SW1.2
unnamed: D1.1, JP2.5, U1.3, U1.10
unnamed: JP2.3, U1.4
unnamed: JP1.2, JP2.1, R2.1
unnamed: JP2.2, JP2.4, JP2.6, R3.2, U1.1
unnamed: JP1.3, U1.5, U1.8
VDD: C2.1, C3.1, D5.2, LDR1.1, R3.1, RV1.3, SW1.1, U1.14
VSS: C2.2, C3.2, D2.1, D4.1, P1.4, Q1.S, R1.2, U1.7

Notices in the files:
board/hv-powersupply.kicad_pcb:
Copyright (c) 2014 Andreas Messer
board/mppt-loader.kicad_pcb:
Copyright (c) 2015 Andreas Messer
board/twilightswitch.kicad_pcb:
Copyright (c) 2013
